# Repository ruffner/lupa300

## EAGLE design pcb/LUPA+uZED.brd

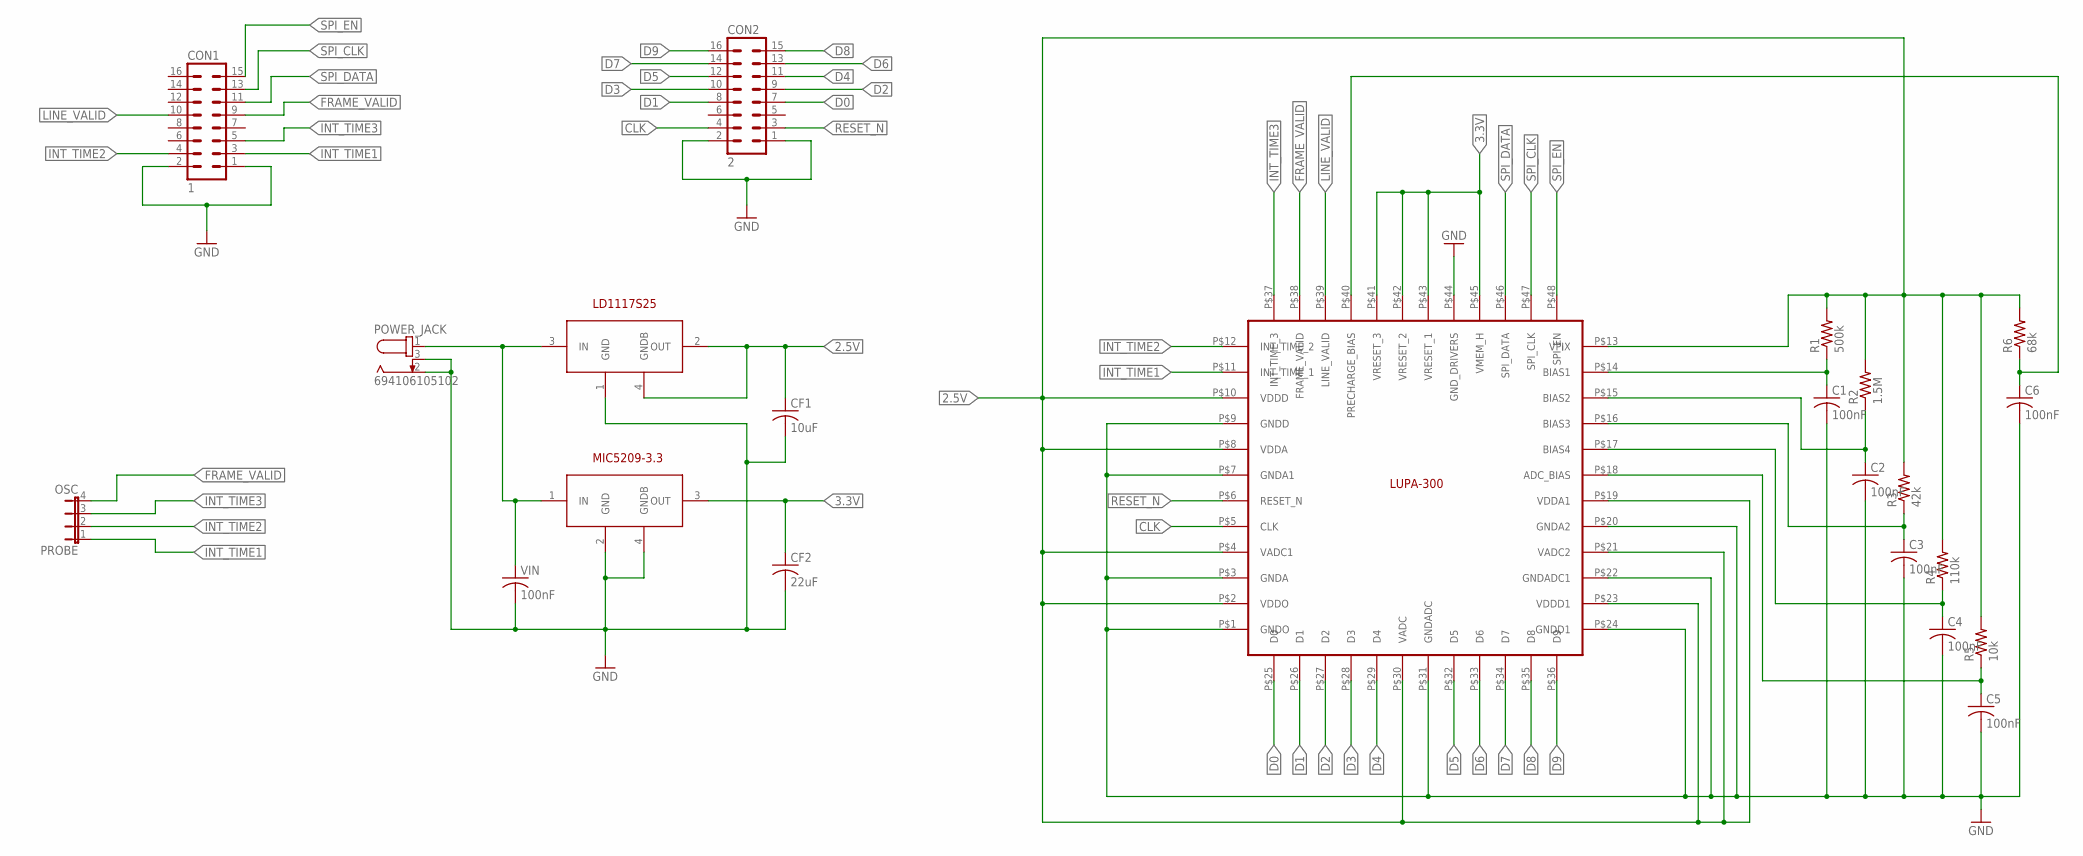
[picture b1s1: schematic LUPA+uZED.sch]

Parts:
C1, C2, C3, C4, C5, C6: 100nF; C3216
CF1: 10uF; C3216
CF2: 22uF; C3216
CON1: 1; MA08-2
CON2: 2; MA08-2
POWER_JACK: 694106105102
PROBE: OSC; JP4
R1: 500k; R1206
R2: 1.5M; R1206
R3: 42k; R1206
R4: 110k; R1206
R5: 10k; R1206
R6: 68k; R1206
U$1: IS; LUPA300
U$2: LD1117S25; SOT223
U$3: MIC5209-3.3; SOT223
VIN: 100nF; C3216

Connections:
2.5V: CF1.1, R1.2, R2.2, R3.2, R4.2, R5.2, R6.2, U$1.P$2 (VDDO), U$1.P$4 (VADC1), U$1.P$8 (VDDA), U$1.P$10 (VDDD), U$1.P$13 (VPIX), U$1.P$19 (VDDA1), U$1.P$21 (VADC2), U$1.P$23 (VDDD1), U$1.P$30 (VADC), U$2.2 (OUT), U$2.4 (GNDB)
3.3V: CF2.1, U$1.P$41 (VRESET_3), U$1.P$42 (VRESET_2), U$1.P$43 (VRESET_1), U$1.P$45 (VMEM_H), U$3.3 (OUT)
CLK: CON2.4, U$1.P$5 (CLK)
D0: CON2.7, U$1.P$25 (D0)
D1: CON2.8, U$1.P$26 (D1)
D2: CON2.9, U$1.P$27 (D2)
D3: CON2.10, U$1.P$28 (D3)
D4: CON2.11, U$1.P$29 (D4)
D5: CON2.12, U$1.P$32 (D5)
D6: CON2.13, U$1.P$33 (D6)
D7: CON2.14, U$1.P$34 (D7)
D8: CON2.15, U$1.P$35 (D8)
D9: CON2.16, U$1.P$36 (D9)
FRAME_VALID: CON1.9, PROBE.4, U$1.P$38 (FRAME_VALID)
GND: C1.2, C2.2, C3.2, C4.2, C5.2, C6.2, CF1.2, CF2.2, CON1.1, CON1.2, CON2.1, CON2.2, POWER_JACK.2, POWER_JACK.3, U$1.P$1 (GNDO), U$1.P$3 (GNDA), U$1.P$7 (GNDA1), U$1.P$9 (GNDD), U$1.P$20 (GNDA2), U$1.P$22 (GNDADC1), U$1.P$24 (GNDD1), U$1.P$31 (GNDADC), U$1.P$44 (GND_DRIVERS), U$2.1 (GND), U$3.2 (GND), U$3.4 (GNDB), VIN.2
INT_TIME1: CON1.3, PROBE.1, U$1.P$11 (INT_TIME_1)
INT_TIME2: CON1.4, PROBE.2, U$1.P$12 (INT_TIME_2)
INT_TIME3: CON1.5, PROBE.3, U$1.P$37 (INT_TIME_3)
LINE_VALID: CON1.10, U$1.P$39 (LINE_VALID)
unnamed: C1.1, R1.1, U$1.P$14 (BIAS1)
unnamed: C2.1, R2.1, U$1.P$15 (BIAS2)
unnamed: C4.1, R4.1, U$1.P$17 (BIAS4)
unnamed: C3.1, R3.1, U$1.P$16 (BIAS3)
unnamed: C5.1, R5.1, U$1.P$18 (ADC_BIAS)
unnamed: C6.1, R6.1, U$1.P$40 (PRECHARGE_BIAS)
unnamed: POWER_JACK.1, U$2.3 (IN), U$3.1 (IN), VIN.1
RESET_N: CON2.3, U$1.P$6 (RESET_N)
SPI_CLK: CON1.13, U$1.P$47 (SPI_CLK)
SPI_DATA: CON1.11, U$1.P$46 (SPI_DATA)
SPI_EN: CON1.15, U$1.P$48 (SPI_EN)

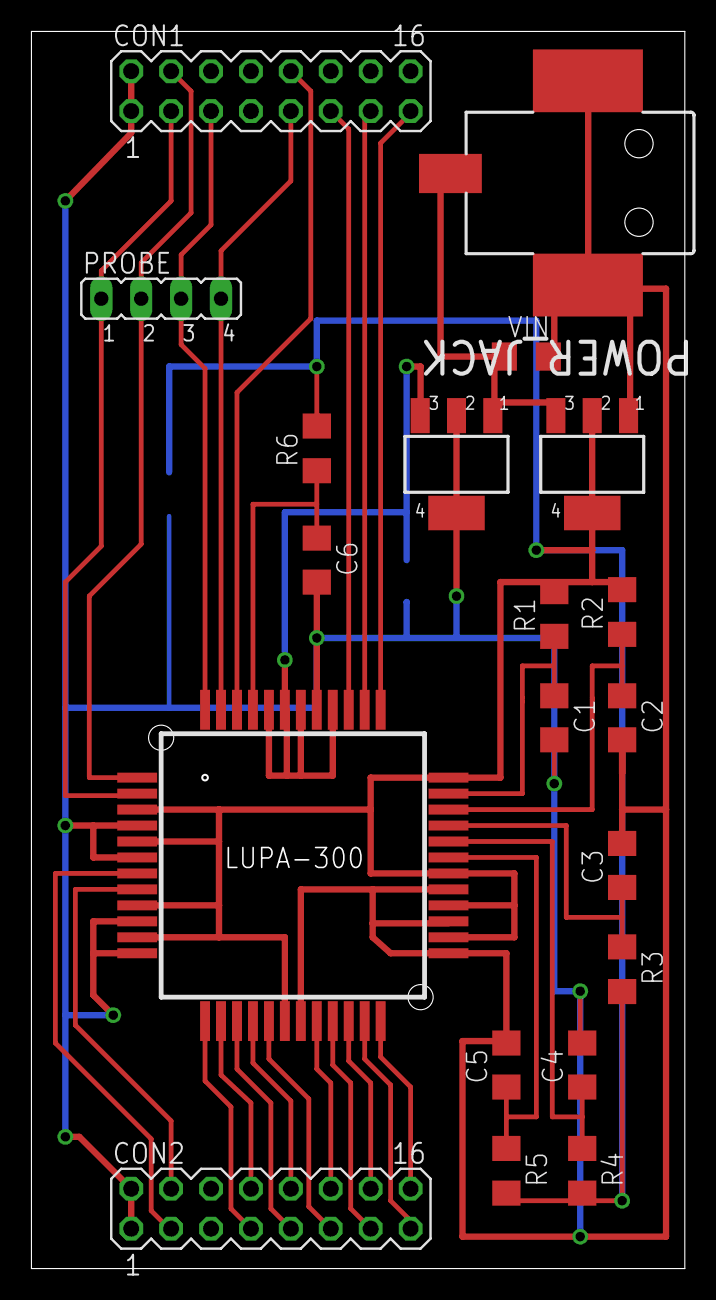
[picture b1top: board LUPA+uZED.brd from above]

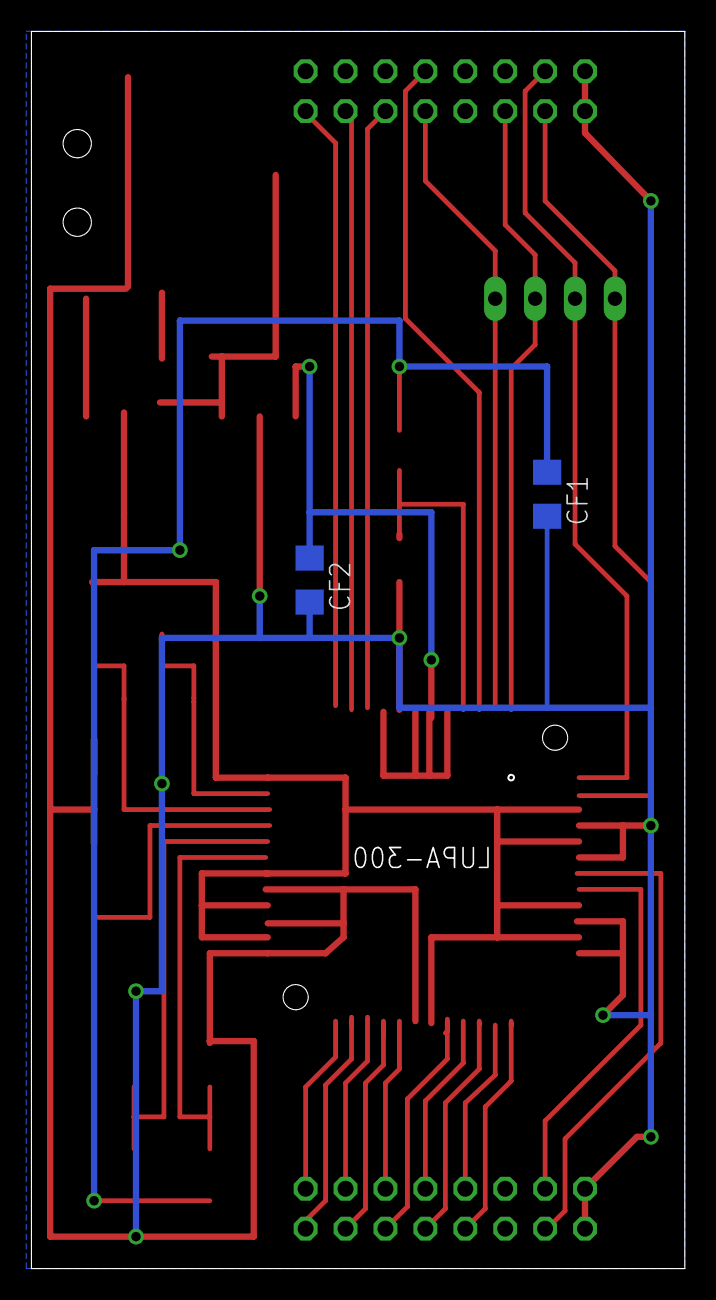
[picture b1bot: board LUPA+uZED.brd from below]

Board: 2 copper layers, 41.6 x 78.7 mm, 22 parts (2 on the bottom side), 30 nets.

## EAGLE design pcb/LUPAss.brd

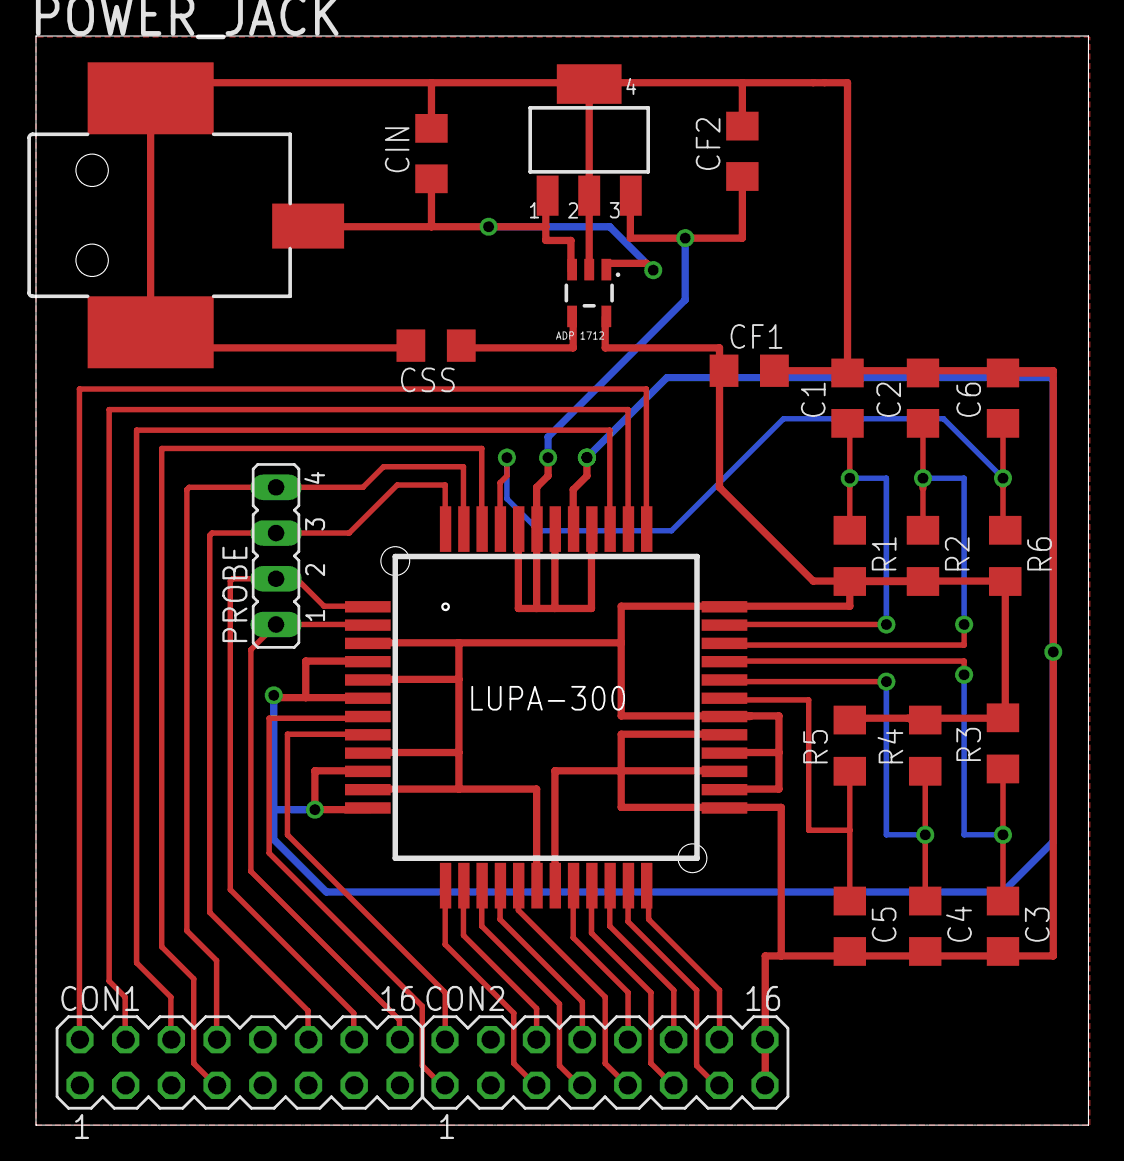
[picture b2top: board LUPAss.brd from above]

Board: 2 copper layers, 58.5 x 60.5 mm, 23 parts (0 on the bottom side), 31 nets.

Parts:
C1, C2, C3, C4, C5, C6: 100nF; C3216
CF1: 2.2uF; C3216
CF2: 22uF; C3216
CIN: 2.2uF; C3216
CON1: 1; MA08-2
CON2: 2; MA08-2
CSS: 2pF; C3216
POWER_JACK: 694106105102
PROBE: OSC; JP4
R1: 500k; R1206
R2: 1.5M; R1206
R3: 42k; R1206
R4: 110k; R1206
R5: 10k; R1206
R6: 68k; R1206
U$1: IS; LUPA300
U$2: ADP1712; SOT23-5
U$3: MIC5209-3.3; SOT223

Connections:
2.5V: CF1.1, R1.2, R2.2, R3.2, R4.2, R5.2, R6.2, U$1.P$2, U$1.P$4, U$1.P$8, U$1.P$10, U$1.P$13, U$1.P$19, U$1.P$21, U$1.P$23, U$1.P$30, U$2.5
3.3V: CF2.1, U$1.P$41, U$1.P$42, U$1.P$43, U$1.P$45, U$3.3
CLK: CON2.2, U$1.P$5
D0: CON2.5, U$1.P$25
D1: CON2.6, U$1.P$26
D2: CON2.7, U$1.P$27
D3: CON2.8, U$1.P$28
D4: CON2.9, U$1.P$29
D5: CON2.10, U$1.P$32
D6: CON2.11, U$1.P$33
D7: CON2.12, U$1.P$34
D8: CON2.13, U$1.P$35
D9: CON2.14, U$1.P$36
FRAME_VALID: CON1.8, PROBE.4, U$1.P$38
GND: C1.2, C2.2, C3.2, C4.2, C5.2, C6.2, CF1.2, CF2.2, CIN.2, CON2.15, CON2.16, CSS.2, POWER_JACK.2, POWER_JACK.3, U$1.P$1, U$1.P$3, U$1.P$7, U$1.P$9, U$1.P$20, U$1.P$22, U$1.P$24, U$1.P$31, U$1.P$44, U$2.2, U$3.2, U$3.4
IN: CIN.1, POWER_JACK.1, U$2.1, U$2.3, U$3.1
INT_TIME1: CON1.16, PROBE.1, U$1.P$11
INT_TIME2: CON1.14, PROBE.2, U$1.P$12
INT_TIME3: CON1.12, PROBE.3, U$1.P$37
LINE_VALID: CON1.7, U$1.P$39
unnamed: C1.1, R1.1, U$1.P$14
unnamed: C2.1, R2.1, U$1.P$15
unnamed: C4.1, R4.1, U$1.P$17
unnamed: C3.1, R3.1, U$1.P$16
unnamed: C5.1, R5.1, U$1.P$18
unnamed: C6.1, R6.1, U$1.P$40
RESET_N: CON2.1, U$1.P$6
SPI_CLK: CON1.4, U$1.P$47
SPI_DATA: CON1.6, U$1.P$46
SPI_EN: CON1.2, U$1.P$48
SS: CSS.1, U$2.4

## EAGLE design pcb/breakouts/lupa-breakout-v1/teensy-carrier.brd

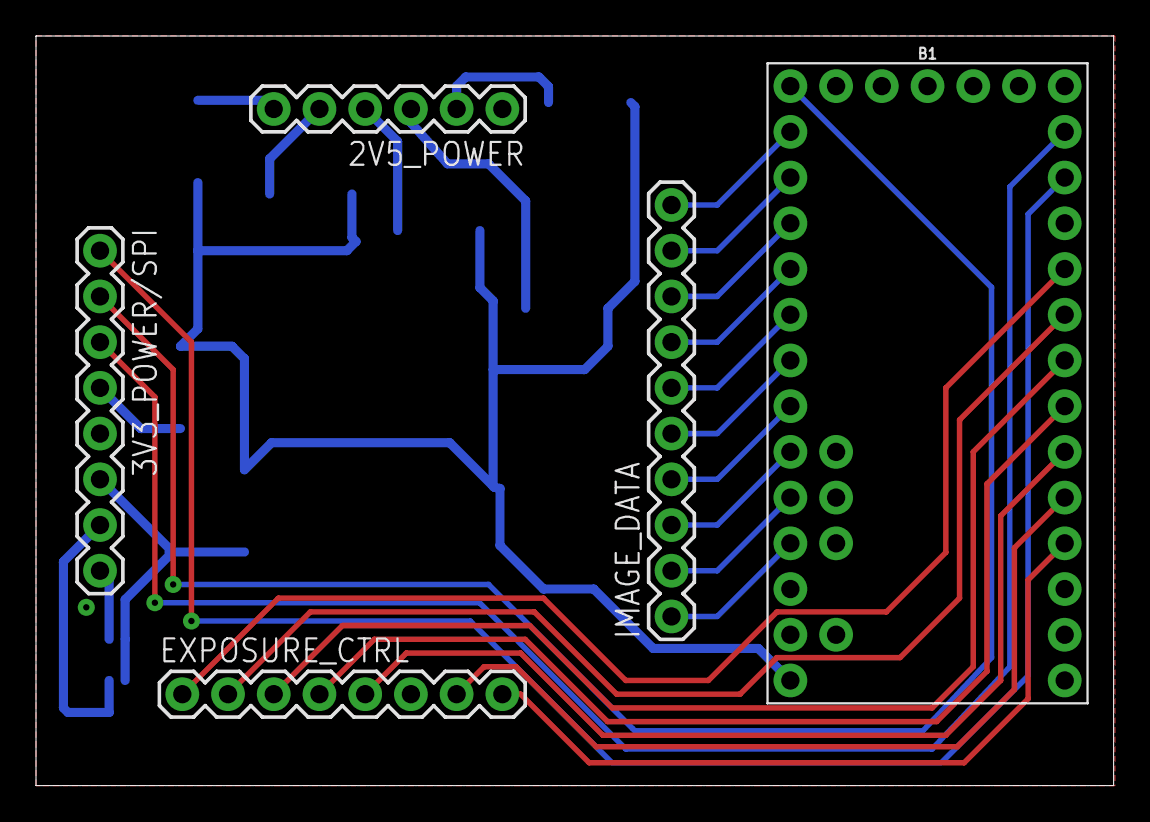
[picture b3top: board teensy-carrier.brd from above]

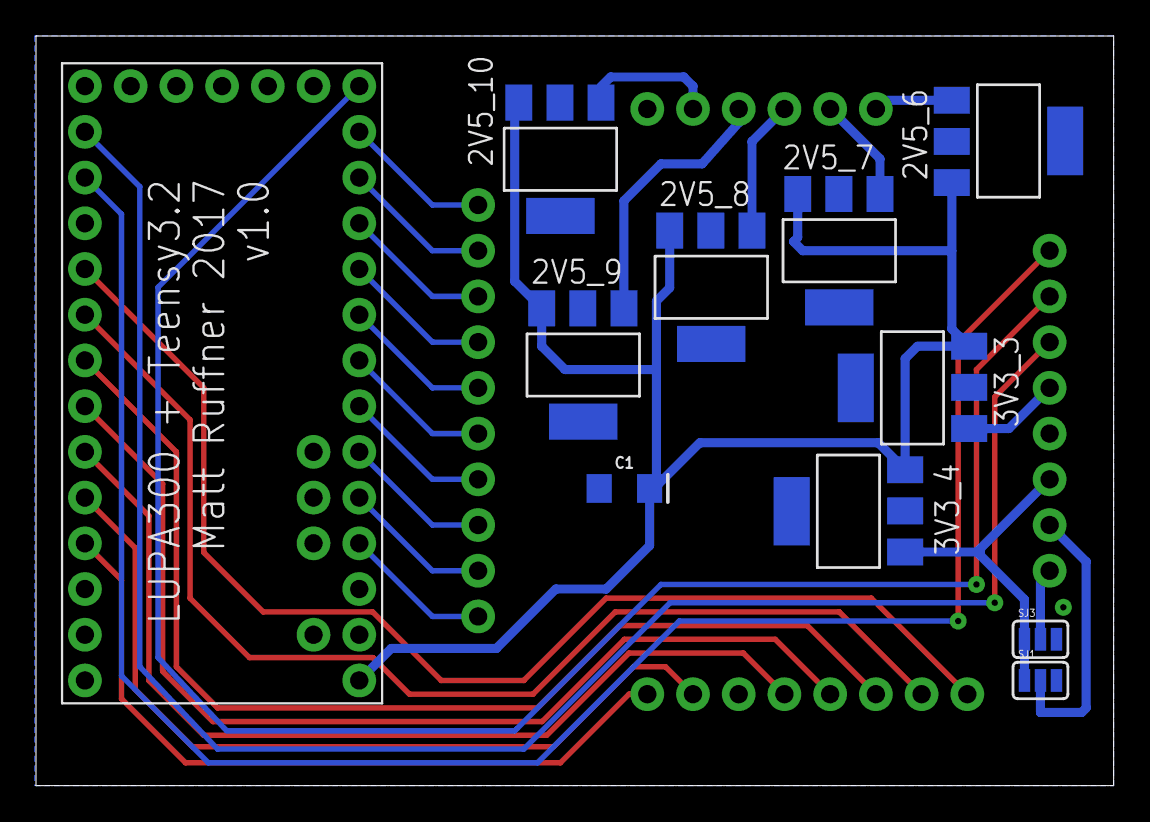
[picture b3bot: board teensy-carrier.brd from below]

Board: 2 copper layers, 59.9 x 41.6 mm, 15 parts (10 on the bottom side), 31 nets.

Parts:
2V5_6, 2V5_7, 2V5_8, 2V5_9, 2V5_10, 3V3_3, 3V3_4: REG1118; SOT223
2V5_POWER: 1X06
3V3_POWER/SPI: 1X08_ROUND
B1: TEENSY-3.1NOSILK; TEENSY-3.1_NOSILK
C1: 10uF; EIA3216
EXPOSURE_CTRL: 1X08_ROUND
IMAGE_DATA: 1X10
SJ1, SJ3: SJ_3

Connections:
CLK: B1.2, EXPOSURE_CTRL.8
D0: B1.23, IMAGE_DATA.1
D1: B1.22, IMAGE_DATA.2
D2: B1.21, IMAGE_DATA.3
D3: B1.20, IMAGE_DATA.4
D4: B1.19, IMAGE_DATA.5
D5: B1.18, IMAGE_DATA.6
D6: B1.17, IMAGE_DATA.7
D7: B1.16, IMAGE_DATA.8
D8: B1.15, IMAGE_DATA.9
D9: B1.14, IMAGE_DATA.10
FRAME_VALID: B1.7, EXPOSURE_CTRL.2
GND: 2V5_6.2, 2V5_7.2, 2V5_8.2, 2V5_9.2, 2V5_10.2, 2V5_POWER.1, 3V3_3.2, 3V3_4.2, 3V3_POWER/SPI.5, B1.GND, C1.-, EXPOSURE_CTRL.6, SJ1.3, SJ3.3
INT_TIME1: B1.4, EXPOSURE_CTRL.5
INT_TIME2: B1.5, EXPOSURE_CTRL.4
INT_TIME3: B1.6, EXPOSURE_CTRL.3
LINE_VALID: B1.8, EXPOSURE_CTRL.1
RESET: B1.3, EXPOSURE_CTRL.7
SPI_CLK: 3V3_POWER/SPI.2, B1.13
SPI_DATA: 3V3_POWER/SPI.3, B1.11
SPI_EN: 3V3_POWER/SPI.1, B1.10
VADC: 2V5_8.1, 2V5_POWER.4
VDDA: 2V5_7.1, 2V5_POWER.5
VDDD: 2V5_9.1, 2V5_POWER.3
VDDO: 2V5_10.1, 2V5_POWER.2
VIN: 2V5_6.3, 2V5_7.3, 2V5_8.3, 2V5_9.3, 2V5_10.3, 3V3_3.3, 3V3_4.3, B1.VIN, C1.+
VMEM_H: 3V3_3.1, 3V3_POWER/SPI.4
VPIX: 2V5_6.1, 2V5_POWER.6
VRESET_1: 3V3_4.1, 3V3_POWER/SPI.6, SJ1.1, SJ3.1
VRESET_2: 3V3_POWER/SPI.7, SJ1.2
VRESET_3: 3V3_POWER/SPI.8, SJ3.2

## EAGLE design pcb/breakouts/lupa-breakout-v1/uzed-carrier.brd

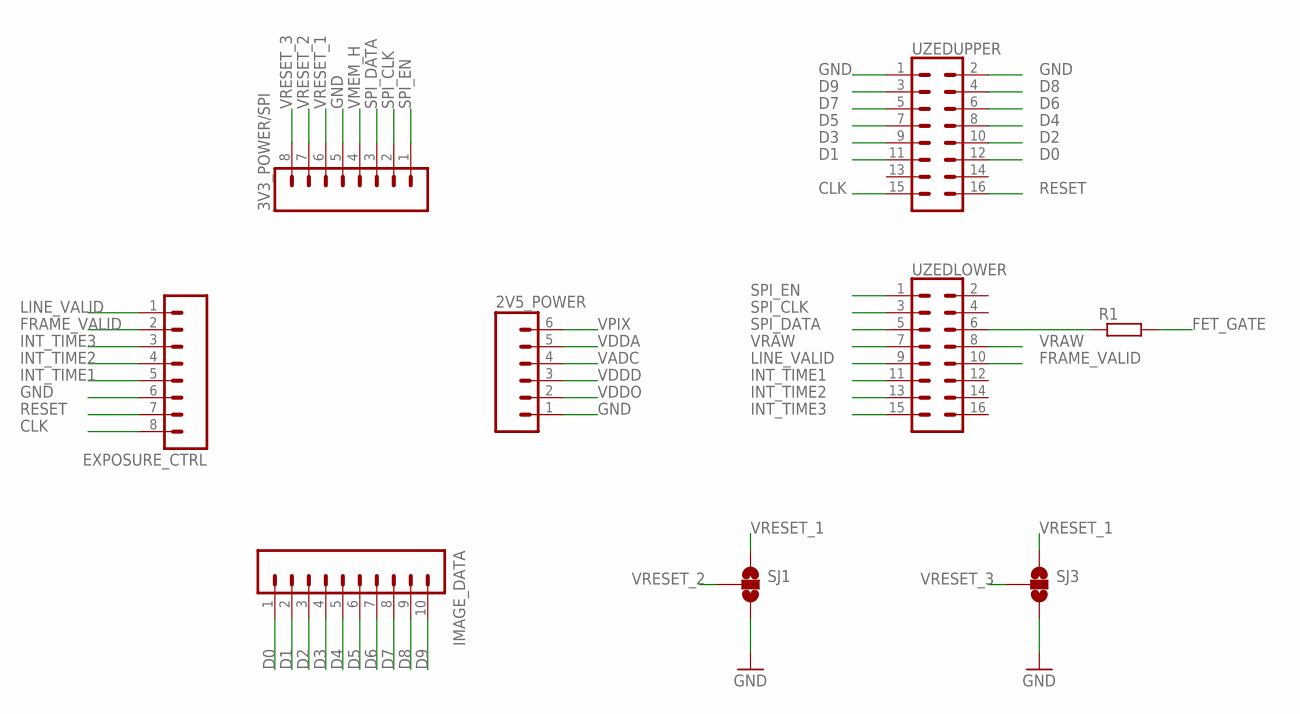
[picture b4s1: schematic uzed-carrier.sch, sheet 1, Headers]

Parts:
2V5_POWER: M06SILK_FEMALE_PTH; 1X06
3V3_POWER/SPI: M08; 1X08_ROUND
EXPOSURE_CTRL: M08; 1X08_ROUND
IMAGE_DATA: M10SILK_FEMALE_PTH; 1X10
R1: R-EU_M1206; M1206
SJ1, SJ3: SOLDERJUMPER_2WAYS; SJ_3
UZEDLOWER: CONN_08X2; 2X8
UZEDUPPER: CONN_08X2; 2X8

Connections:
CLK: EXPOSURE_CTRL.8, UZEDUPPER.15
D0: IMAGE_DATA.1, UZEDUPPER.12
D1: IMAGE_DATA.2, UZEDUPPER.11
D2: IMAGE_DATA.3, UZEDUPPER.10
D3: IMAGE_DATA.4, UZEDUPPER.9
D4: IMAGE_DATA.5, UZEDUPPER.8
D5: IMAGE_DATA.6, UZEDUPPER.7
D6: IMAGE_DATA.7, UZEDUPPER.6
D7: IMAGE_DATA.8, UZEDUPPER.5
D8: IMAGE_DATA.9, UZEDUPPER.4
D9: IMAGE_DATA.10, UZEDUPPER.3
FET_GATE: R1.2; also elsewhere on the board
FRAME_VALID: EXPOSURE_CTRL.2, UZEDLOWER.10
GND: 2V5_POWER.1, 3V3_POWER/SPI.5, EXPOSURE_CTRL.6, SJ1.3, SJ3.3, UZEDUPPER.1, UZEDUPPER.2; also elsewhere on the board
INT_TIME1: EXPOSURE_CTRL.5, UZEDLOWER.11
INT_TIME2: EXPOSURE_CTRL.4, UZEDLOWER.13
INT_TIME3: EXPOSURE_CTRL.3, UZEDLOWER.15
LINE_VALID: EXPOSURE_CTRL.1, UZEDLOWER.9
unnamed: R1.1, UZEDLOWER.6
RESET: EXPOSURE_CTRL.7, UZEDUPPER.16
SPI_CLK: 3V3_POWER/SPI.2, UZEDLOWER.3
SPI_DATA: 3V3_POWER/SPI.3, UZEDLOWER.5
SPI_EN: 3V3_POWER/SPI.1, UZEDLOWER.1
VADC: 2V5_POWER.4; also elsewhere on the board
VDDA: 2V5_POWER.5; also elsewhere on the board
VDDD: 2V5_POWER.3; also elsewhere on the board
VDDO: 2V5_POWER.2; also elsewhere on the board
VMEM_H: 3V3_POWER/SPI.4; also elsewhere on the board
VPIX: 2V5_POWER.6; also elsewhere on the board
VRAW: UZEDLOWER.7, UZEDLOWER.8; also elsewhere on the board
VRESET_1: 3V3_POWER/SPI.6, SJ1.1, SJ3.1; also elsewhere on the board
VRESET_2: 3V3_POWER/SPI.7, SJ1.2
VRESET_3: 3V3_POWER/SPI.8, SJ3.2

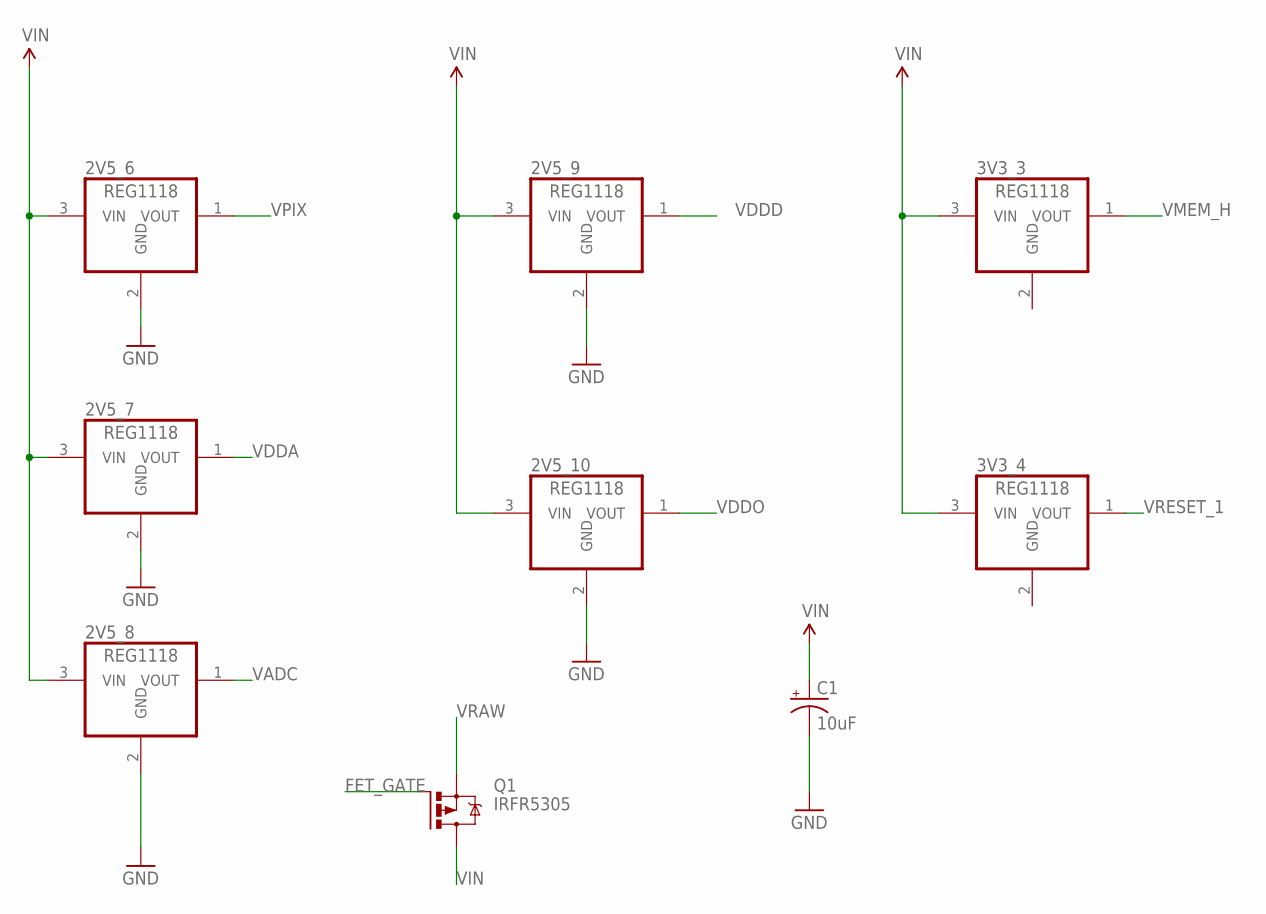
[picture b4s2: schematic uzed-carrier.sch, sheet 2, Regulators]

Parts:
2V5_6, 2V5_7, 2V5_8, 2V5_9, 2V5_10, 3V3_3, 3V3_4: REG1118; SOT223
C1: 10uF; EIA3216
Q1: IRFR5305; D-PAK_TO252AA

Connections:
FET_GATE: Q1.1 (G); also elsewhere on the board
GND: 2V5_6.2 (GND), 2V5_7.2 (GND), 2V5_8.2 (GND), 2V5_9.2 (GND), 2V5_10.2 (GND), 3V3_3.2 (GND), 3V3_4.2 (GND), C1.-; also elsewhere on the board
VADC: 2V5_8.1 (VOUT); also elsewhere on the board
VDDA: 2V5_7.1 (VOUT); also elsewhere on the board
VDDD: 2V5_9.1 (VOUT); also elsewhere on the board
VDDO: 2V5_10.1 (VOUT); also elsewhere on the board
VIN: 2V5_6.3 (VIN), 2V5_7.3 (VIN), 2V5_8.3 (VIN), 2V5_9.3 (VIN), 2V5_10.3 (VIN), 3V3_3.3 (VIN), 3V3_4.3 (VIN), C1.+, Q1.4 (D)
VMEM_H: 3V3_3.1 (VOUT); also elsewhere on the board
VPIX: 2V5_6.1 (VOUT); also elsewhere on the board
VRAW: Q1.3 (S); also elsewhere on the board
VRESET_1: 3V3_4.1 (VOUT); also elsewhere on the board

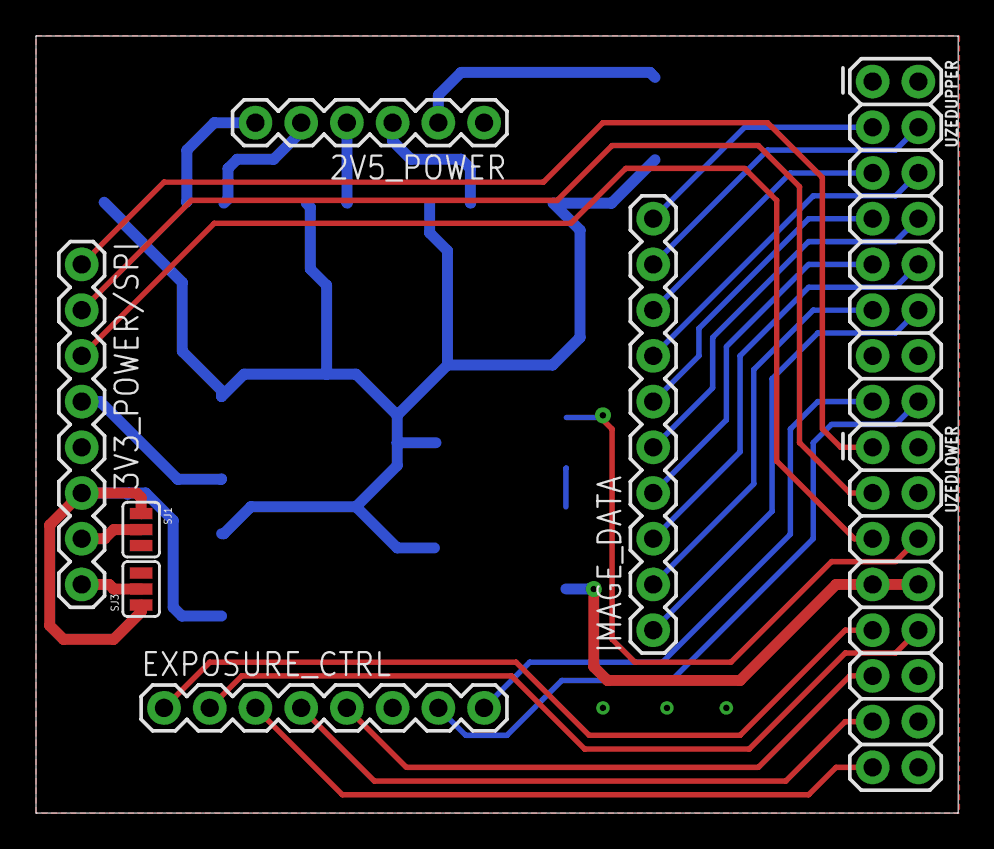
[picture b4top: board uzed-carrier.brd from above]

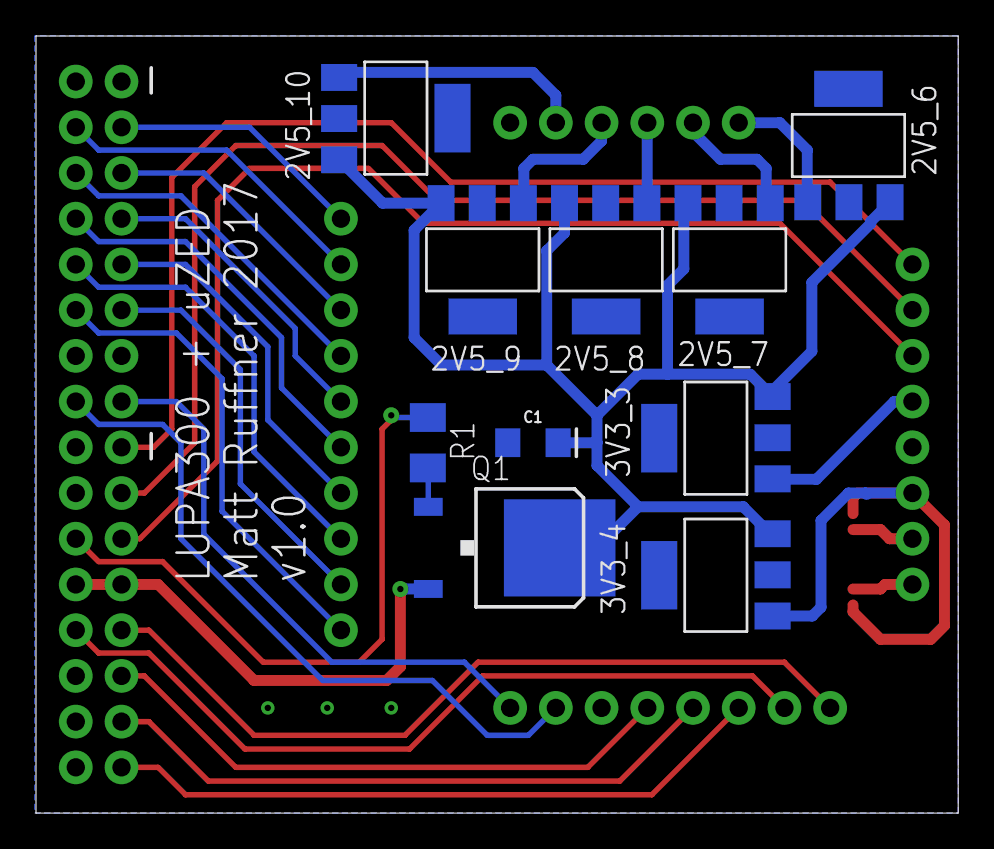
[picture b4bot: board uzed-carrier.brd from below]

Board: 2 copper layers, 51.2 x 43.2 mm, 18 parts (10 on the bottom side), 34 nets.

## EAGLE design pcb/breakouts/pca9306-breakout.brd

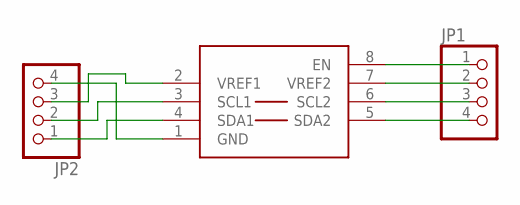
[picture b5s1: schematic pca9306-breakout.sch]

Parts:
JP1, JP2: PINHD-1X4; 1X04
U11: PCA9306; PSOP-8

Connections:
GND: JP2.4, U11.1 (GND)
unnamed: JP2.1, U11.4 (SDA1)
unnamed: JP2.2, U11.3 (SCL1)
unnamed: JP2.3, U11.2 (VREF1)
unnamed: JP1.1, U11.8 (EN)
unnamed: JP1.2, U11.7 (VREF2)
unnamed: JP1.3, U11.6 (SCL2)
unnamed: JP1.4, U11.5 (SDA2)

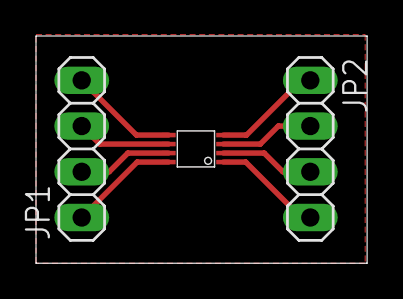
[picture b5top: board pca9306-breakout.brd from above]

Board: 2 copper layers, 18.4 x 12.6 mm, 3 parts (0 on the bottom side), 8 nets.

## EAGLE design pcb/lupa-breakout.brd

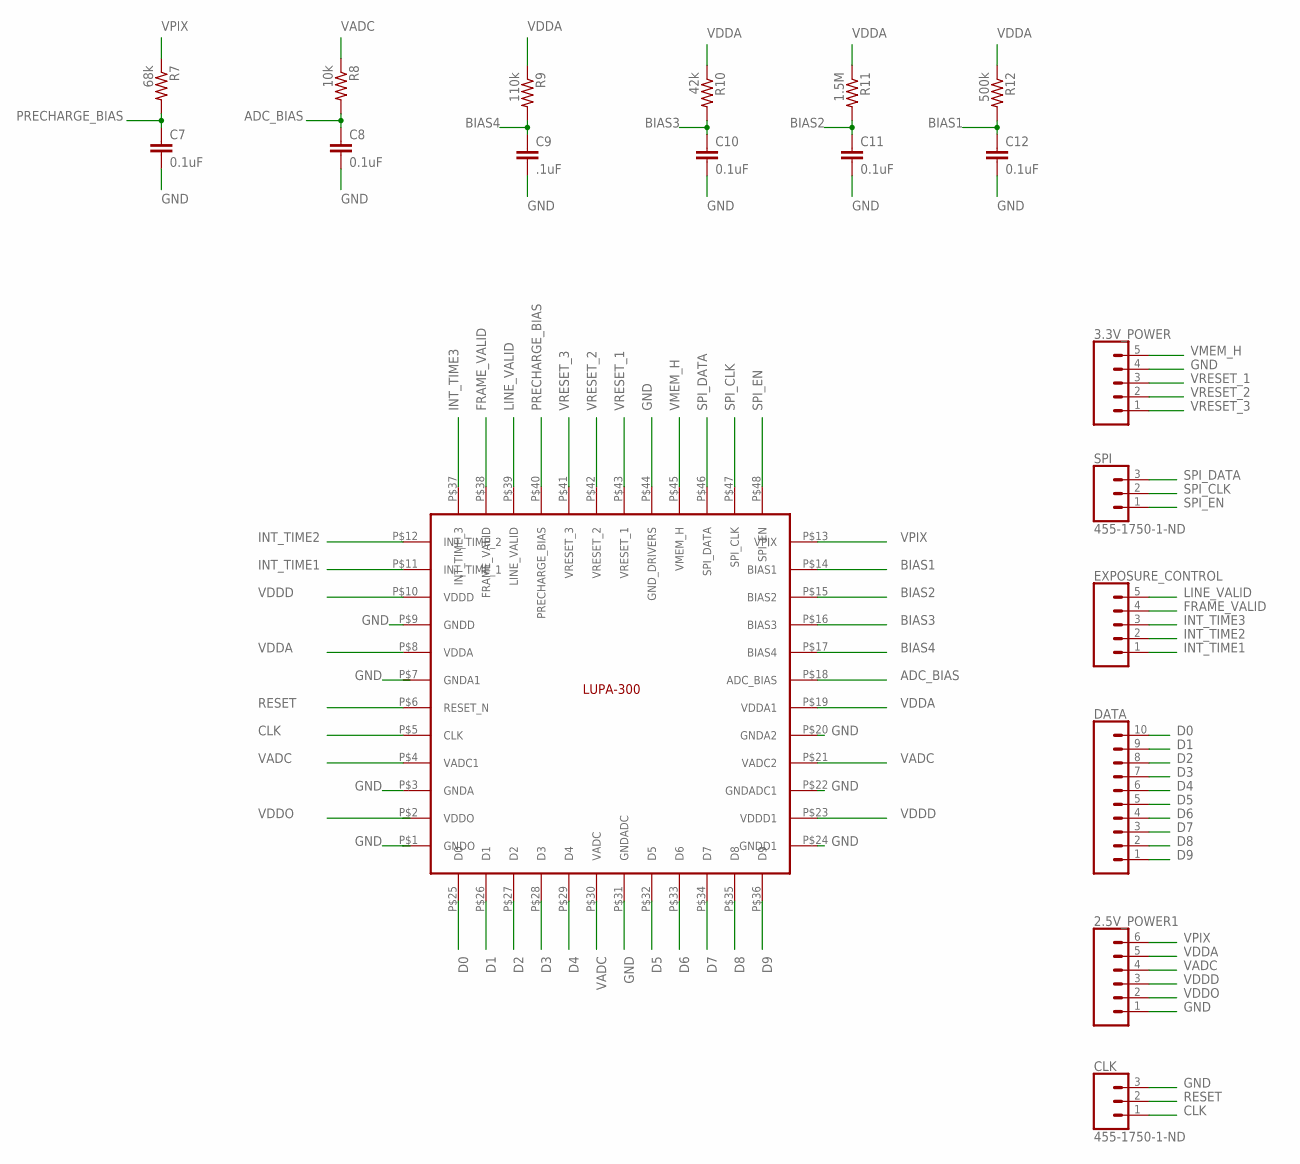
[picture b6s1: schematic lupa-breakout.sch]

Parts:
2.5V_POWER1: CONN_06SILK_FEMALE_PTH; 1X06
3.3V_POWER: CONN_05; 1X05
C7, C8, C10, C11, C12: 0.1uF; C1206
C9: .1uF; C1206
CLK: 455-1750-1-ND; 1X03
DATA: CONN_10"; 1X10
EXPOSURE_CONTROL: CONN_05; 1X05
R7: 68k; M1206
R8: 10k; M1206
R9: 110k; M1206
R10: 42k; M1206
R11: 1.5M; M1206
R12: 500k; M1206
SPI: 455-1750-1-ND; 1X03
U$1: LUPA300

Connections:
ADC_BIAS: C8.1, R8.2, U$1.P$18 (ADC_BIAS)
BIAS1: C12.1, R12.2, U$1.P$14 (BIAS1)
BIAS2: C11.1, R11.2, U$1.P$15 (BIAS2)
BIAS3: C10.1, R10.2, U$1.P$16 (BIAS3)
BIAS4: C9.1, R9.2, U$1.P$17 (BIAS4)
CLK: CLK.1, U$1.P$5 (CLK)
D0: DATA.10, U$1.P$25 (D0)
D1: DATA.9, U$1.P$26 (D1)
D2: DATA.8, U$1.P$27 (D2)
D3: DATA.7, U$1.P$28 (D3)
D4: DATA.6, U$1.P$29 (D4)
D5: DATA.5, U$1.P$32 (D5)
D6: DATA.4, U$1.P$33 (D6)
D7: DATA.3, U$1.P$34 (D7)
D8: DATA.2, U$1.P$35 (D8)
D9: DATA.1, U$1.P$36 (D9)
FRAME_VALID: EXPOSURE_CONTROL.4, U$1.P$38 (FRAME_VALID)
GND: 2.5V_POWER1.1, 3.3V_POWER.4, C7.2, C8.2, C9.2, C10.2, C11.2, C12.2, CLK.3, U$1.P$1 (GNDO), U$1.P$3 (GNDA), U$1.P$9 (GNDD), U$1.P$20 (GNDA2), U$1.P$22 (GNDADC1), U$1.P$24 (GNDD1), U$1.P$31 (GNDADC), U$1.P$44 (GND_DRIVERS)
INT_TIME1: EXPOSURE_CONTROL.1, U$1.P$11 (INT_TIME_1)
INT_TIME2: EXPOSURE_CONTROL.2, U$1.P$12 (INT_TIME_2)
INT_TIME3: EXPOSURE_CONTROL.3, U$1.P$37 (INT_TIME_3)
LINE_VALID: EXPOSURE_CONTROL.5, U$1.P$39 (LINE_VALID)
PRECHARGE_BIAS: C7.1, R7.2, U$1.P$40 (PRECHARGE_BIAS)
RESET: CLK.2, U$1.P$6 (RESET_N)
SPI_CLK: SPI.2, U$1.P$47 (SPI_CLK)
SPI_DATA: SPI.3, U$1.P$46 (SPI_DATA)
SPI_EN: SPI.1, U$1.P$48 (SPI_EN)
VADC: 2.5V_POWER1.4, R8.1, U$1.P$4 (VADC1), U$1.P$21 (VADC2), U$1.P$30 (VADC)
VDDA: 2.5V_POWER1.5, R9.1, R10.1, R11.1, R12.1, U$1.P$8 (VDDA), U$1.P$19 (VDDA1)
VDDD: 2.5V_POWER1.3, U$1.P$10 (VDDD), U$1.P$23 (VDDD1)
VDDO: 2.5V_POWER1.2, U$1.P$2 (VDDO)
VMEM_H: 3.3V_POWER.5, U$1.P$45 (VMEM_H)
VPIX: 2.5V_POWER1.6, R7.1, U$1.P$13 (VPIX)
VRESET_1: 3.3V_POWER.3, U$1.P$43 (VRESET_1)
VRESET_2: 3.3V_POWER.2, U$1.P$42 (VRESET_2)
VRESET_3: 3.3V_POWER.1, U$1.P$41 (VRESET_3)

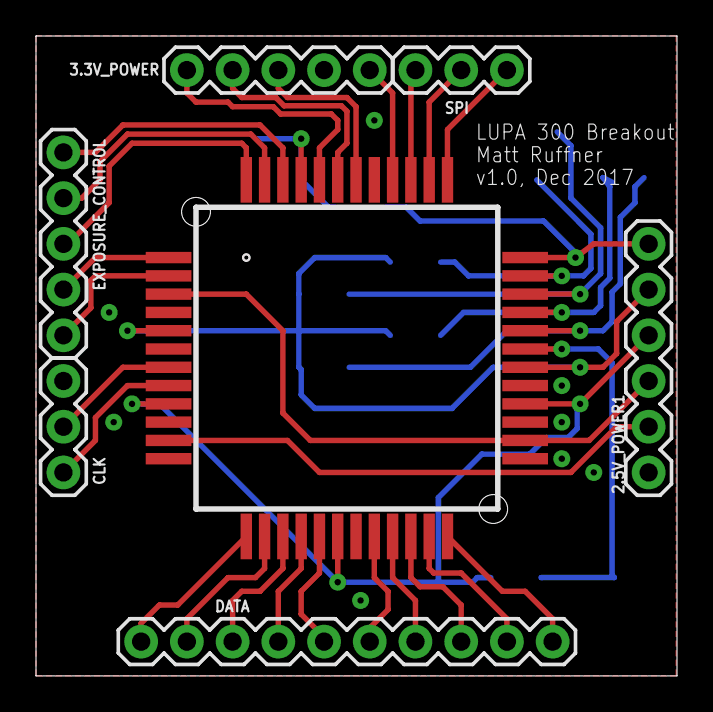
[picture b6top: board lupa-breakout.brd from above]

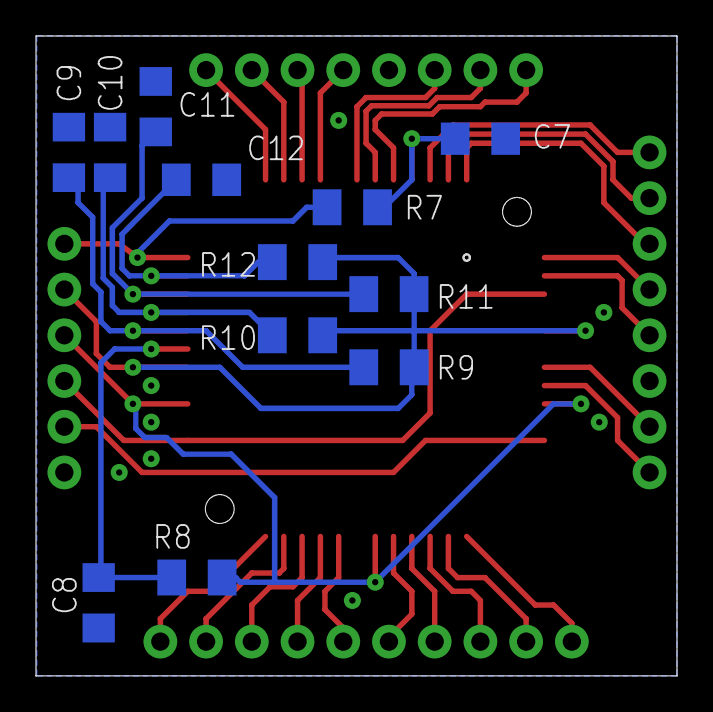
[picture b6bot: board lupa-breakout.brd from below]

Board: 2 copper layers, 35.6 x 35.6 mm, 19 parts (12 on the bottom side), 36 nets.

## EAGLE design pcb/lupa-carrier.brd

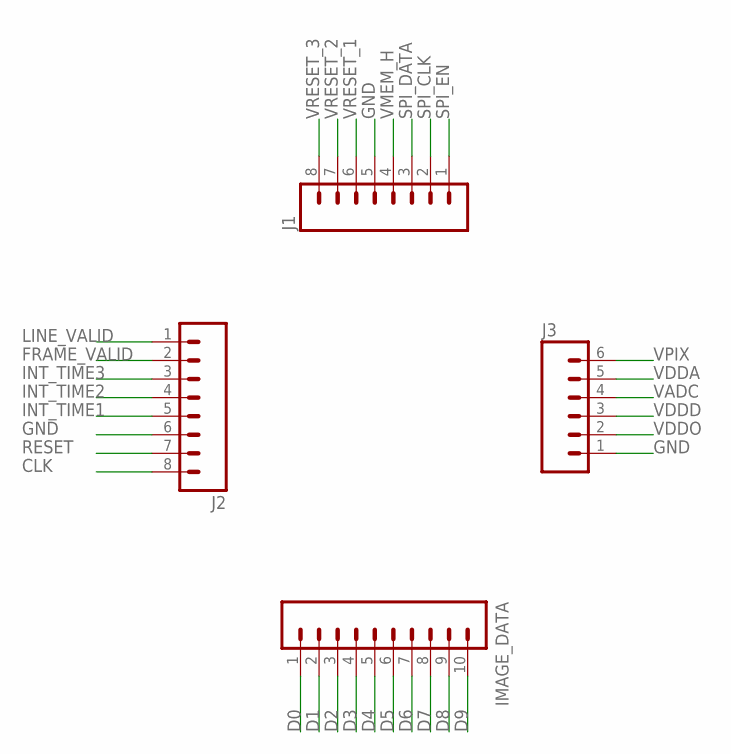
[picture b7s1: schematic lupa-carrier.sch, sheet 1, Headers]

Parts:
IMAGE_DATA: M10SILK_FEMALE_PTH; 1X10
J1, J2: M08; 1X08_ROUND
J3: M06SILK_FEMALE_PTH; 1X06

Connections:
CLK: J2.8
D0: IMAGE_DATA.1
D1: IMAGE_DATA.2
D2: IMAGE_DATA.3
D3: IMAGE_DATA.4
D4: IMAGE_DATA.5
D5: IMAGE_DATA.6
D6: IMAGE_DATA.7
D7: IMAGE_DATA.8
D8: IMAGE_DATA.9
D9: IMAGE_DATA.10
FRAME_VALID: J2.2
GND: J1.5, J2.6, J3.1; also elsewhere on the board
INT_TIME1: J2.5
INT_TIME2: J2.4
INT_TIME3: J2.3
LINE_VALID: J2.1
RESET: J2.7
SPI_CLK: J1.2
SPI_DATA: J1.3
SPI_EN: J1.1
VADC: J3.4; also elsewhere on the board
VDDA: J3.5; also elsewhere on the board
VDDD: J3.3; also elsewhere on the board
VDDO: J3.2; also elsewhere on the board
VMEM_H: J1.4; also elsewhere on the board
VPIX: J3.6; also elsewhere on the board
VRESET_1: J1.6; also elsewhere on the board
VRESET_2: J1.7
VRESET_3: J1.8

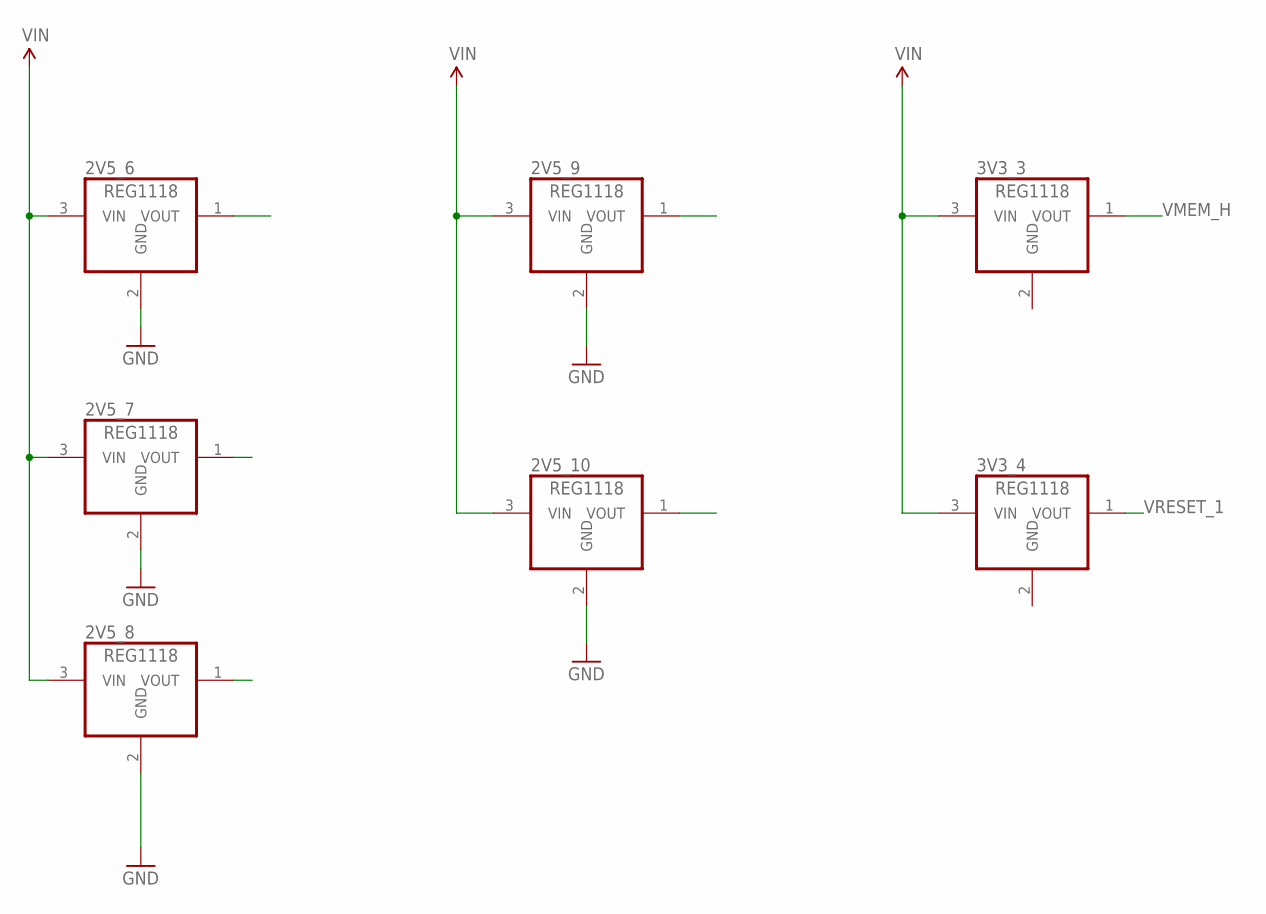
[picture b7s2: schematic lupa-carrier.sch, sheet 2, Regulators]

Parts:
2V5_6, 2V5_7, 2V5_8, 2V5_9, 2V5_10, 3V3_3, 3V3_4: REG1118; SOT223

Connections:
GND: 2V5_6.2 (GND), 2V5_7.2 (GND), 2V5_8.2 (GND), 2V5_9.2 (GND), 2V5_10.2 (GND), 3V3_3.2 (GND), 3V3_4.2 (GND); also elsewhere on the board
VADC: 2V5_8.1 (VOUT); also elsewhere on the board
VDDA: 2V5_7.1 (VOUT); also elsewhere on the board
VDDD: 2V5_9.1 (VOUT); also elsewhere on the board
VDDO: 2V5_10.1 (VOUT); also elsewhere on the board
VIN: 2V5_6.3 (VIN), 2V5_7.3 (VIN), 2V5_8.3 (VIN), 2V5_9.3 (VIN), 2V5_10.3 (VIN), 3V3_3.3 (VIN), 3V3_4.3 (VIN)
VMEM_H: 3V3_3.1 (VOUT); also elsewhere on the board
VPIX: 2V5_6.1 (VOUT); also elsewhere on the board
VRESET_1: 3V3_4.1 (VOUT); also elsewhere on the board

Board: 2 copper layers, 11 parts (0 on the bottom side), 9 nets, no tracks yet.

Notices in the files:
parts and their libraries:
Wurth_Elektronik_Electromechanic_DC_Powe: Copyright: Würth Elektronik
SparkFun-Connectors: Licensing: Creative Commons ShareAlike 4.0 International - https://creativecommons.org/licenses/by-sa/4.0
